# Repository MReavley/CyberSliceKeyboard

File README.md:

# CyberSlice Keyboard

42/36 key split keyboard using RP2040, with the same layout (in 36 key configuration) as my previous design, the Slice 36. The goal was primarily to experience designing a microcontroller directly on the PCB, but I also wanted to try to take advantage of the large number of GPIO pins on the RP2040. There are 8 additional GPIO (2 analog capable) on the PCB with the intention of adding functionality through magnetic pogo connectors, but that is still a work in progress. 

## Features

- Reversible PCB designed for PCB assembly services  
- RP2040 per side, with 16MB of flash  
- Laser cut aluminium plate, custom designed 3D printed case with magnets  
- Footprints for magnetic pogo connectors on each side
- Breakaway tabs convert from 42 to 36 key  

## If you want to build:
This board is just a prototype, and there are a couple pointers to watch out for:

Reversible PCB: Since the PCB is reversible, solder on the trrs connector on opposite sides of the PCB for each half. The USB-C connector for the left half will be on the bottom side, which does necessitate taller rubber feet unfortunately.

Components on the rear:  
These components will not be assembled by basic PCBa, but the parts can be scavenged from spare assembled PCBs (per side)
- C7 (100nF 0603 MLCC capacitor)
- R1 and R2 (5.1k 0603 resistors)
- R12 and R13 (Optional, 4.7k 0603 pullups for split over I2C, not needed for UART)

Additional components:
- PJ320D trrs connectors (x1 per side), solder on opposite side of PCB for the different halves
- 2.54mm magnetic pogo connectors (5 contacts) (2x per side) (optional, can solder directly instead)
- 6mm diameter x 3mm height magnets x6 per side for case (optional, can use screw holes instead)

Reset and boot switches may need to be renamed in the BOM file (not using SW1 and SW2) for them to be auto-selected by PCBa service  
- Otherwise shorting the pads on the PCB will have the same effect

Case:
- Tolerances were very loose on my case, but this does depend on the printer
- Ideally, one would redesign the plate to mount directly to the case (add screw holes)
- Tolerance for the magnet holes can be a bit too tight, probably increase from 6 to 6.1 or 6.2mm diameter

## Things to improve

- Rename the reset and boot switches from SW1 and SW2 to something else to not clash with the names of the switches (caused me to make a mistake in my order)  
- Shift the few SMD parts on the back side to the front for PCBa  
- Add a few more LEDs for status indicators on the PCB itself  
- Change the plate the design for better mounting of PCB and plate to case, or alternatively integrate the plate into the case

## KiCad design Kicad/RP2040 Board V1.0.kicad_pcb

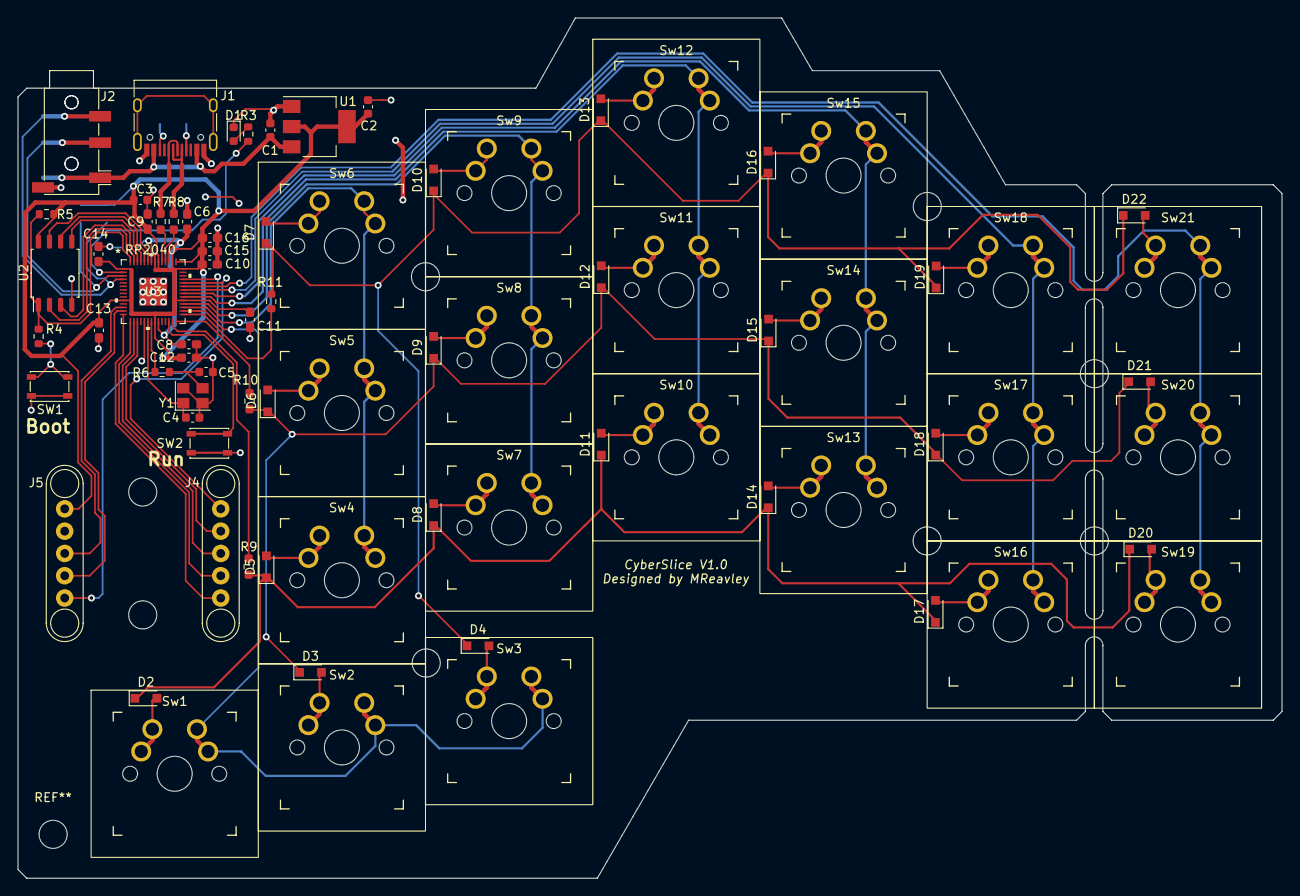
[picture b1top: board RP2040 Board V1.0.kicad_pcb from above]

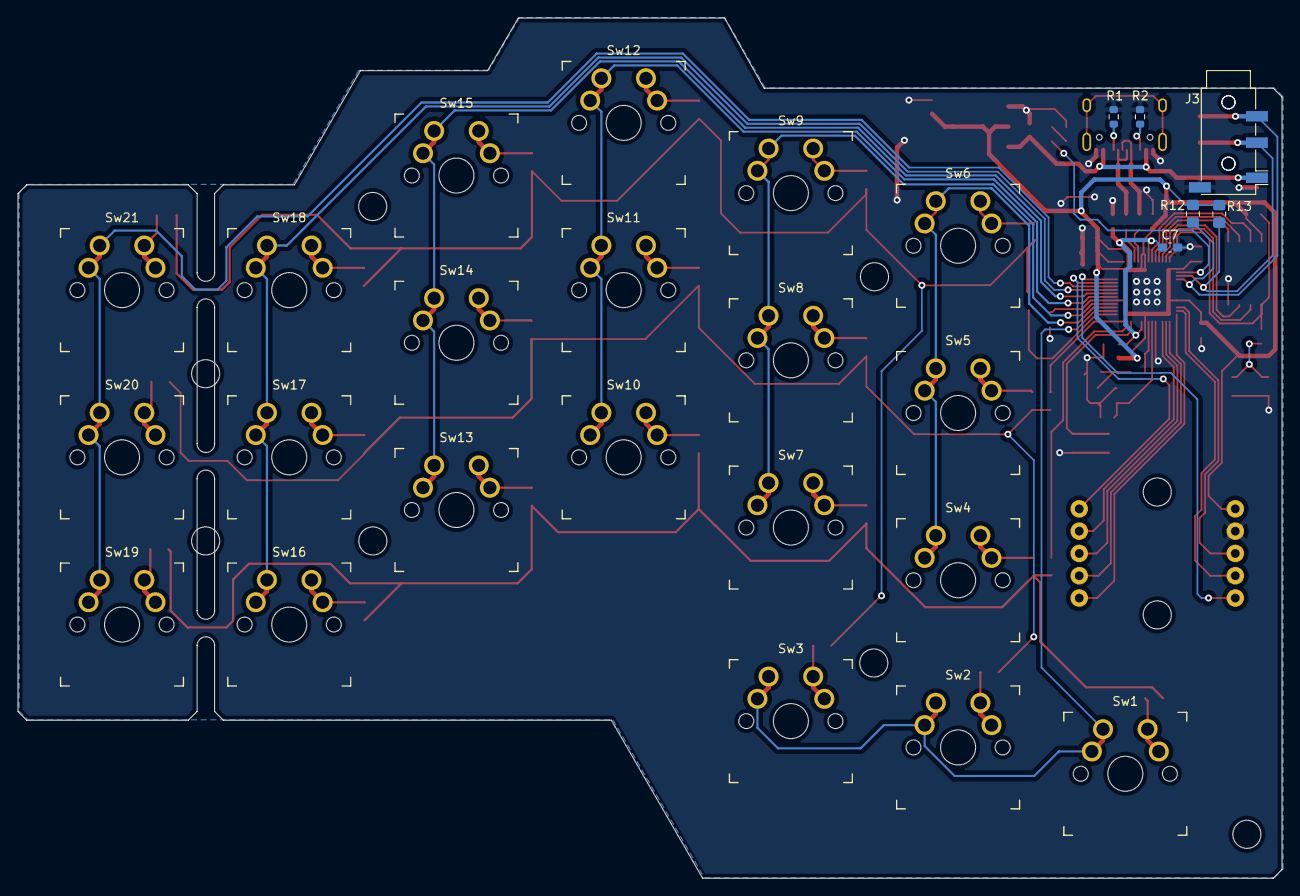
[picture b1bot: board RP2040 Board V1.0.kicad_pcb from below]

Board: 2 copper layers, 144.0 x 98.0 mm, 83 parts (6 on the bottom side), 67 nets.

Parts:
C1, C2: 22u; C_0603_1608Metric
C3: 100n; C_0603_1608Metric
C4, C5: 27p; C_0603_1608Metric
C6, C16: 1u; C_0603_1608Metric_Pad1.08x0.95mm_HandSolder
C7, C8, C9, C10, C11, C12, C13, C14, C15: 100n; C_0603_1608Metric_Pad1.08x0.95mm_HandSolder
D1: RED; LED_0603_1608Metric
D2, D3, D4, D5, D6, D7, D8, D9, D10, D11, D12, D13, D14, D15, D16, D17, D18, D19, D20, D21, D22: D; D_SOD-323_HandSoldering
J1: USB_C_Receptacle_USB2.0; USB_C_Receptacle_HRO_TYPE-C-31-M-12
J2, J3: AudioJack4; Jack_3.5mm_PJ320D_Horizontal
J4, J5: Conn_01x05_MountingPin; Magnet 5pin 2.54mm pitch through hole
R1, R2, R11: 5.1k; R_0603_1608Metric
R3, R4, R6: 1k; R_0603_1608Metric
R5: DNP; R_0603_1608Metric
R7, R8: 27; R_0603_1608Metric_Pad0.98x0.95mm_HandSolder
R9, R10: 5.1k; R_0603_1608Metric_Pad0.98x0.95mm_HandSolder
R12, R13: DNP; R_0805_2012Metric_Pad1.20x1.40mm_HandSolder
SW1, SW2: SW_SPST; SW_SPST_PTS810
Sw1, Sw2, Sw3, Sw4, Sw5, Sw6, Sw7, Sw8, Sw9, Sw10, Sw11, Sw12, Sw13, Sw14, Sw15, Sw16, Sw17, Sw18, Sw19, Sw20, Sw21: Cherry_Doublesided; SW_MX_reversible
U1: AMS1117-3.3; SOT-223-3_TabPin2
U2: W25Q128JVS; SOIC-8_5.23x5.23mm_P1.27mm
U3: RP2040
Y1: 12MHz; Crystal_SMD_3225-4Pin_3.2x2.5mm

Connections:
+1V1: C6.1, C7.1, C8.1, U3.23 (DVDD), U3.45 (VREG_VOUT), U3.50 (DVDD)
+3V3: C2.1, C3.1, C9.1, C10.1, C11.1, C12.1, C13.1, C14.1, C15.1, C16.1, J5.1, R5.2, R12.1, R13.1, U1.2 (VO), U2.8 (VCC), U3.1 (IOVDD), U3.10 (IOVDD), U3.22 (IOVDD), U3.33 (IOVDD), U3.42 (IOVDD), U3.43 (ADC_AVDD), U3.44 (VREG_IN), U3.48 (USB_VDD), U3.49 (IOVDD)
/QSPICLK: U2.6 (CLK), U3.52 (QSPI_SCLK)
/QSPISD0: U2.5 (DI(IO0)), U3.53 (QSPI_SD0)
/QSPISD2: U2.3 (IO2), U3.54 (QSPI_SD2)
/QSPISD3: U2.7 (IO3), U3.51 (QSPI_SD3)
/QSPISS: R4.1, R5.1, U2.1 (~CS), U3.56 (QSPI_SS)
/SQPISD1: U2.2 (DO(IO1)), U3.55 (QSPI_SD1)
Col 0: Sw1.2 (SW), Sw2.2 (SW), Sw3.2 (NW), U3.30 (GPIO19)
Col 1: Sw4.2 (SW), Sw5.2 (NW), Sw6.2 (NW), U3.31 (GPIO20)
Col 2: Sw7.2 (SW), Sw8.2 (NW), Sw9.2 (NW), U3.32 (GPIO21)
Col 3: Sw10.2 (SW), Sw11.2 (NW), Sw12.2 (NW), U3.34 (GPIO22)
Col 4: Sw13.2 (NW), Sw14.2 (NW), Sw15.2 (NW), U3.35 (GPIO23)
Col 5: Sw16.2 (SW), Sw17.2 (NW), Sw18.2 (NW), U3.36 (GPIO24)
Col 6: Sw19.2 (SW), Sw20.2 (SW), Sw21.2 (NW), U3.37 (GPIO25)
Data+: J1.A6 (D+), J1.B6 (D+), R7.2
Data-: J1.A7 (D-), J1.B7 (D-), R8.2
GND: C1.2, C2.2, C3.2, C4.2, C5.2, C6.2, C7.2, C8.2, C9.2, C10.2, C11.2, C12.2, C13.2, C14.2, C15.2, C16.2, D1.1 (K), J1.A1 (GND), J1.A12 (GND), J1.B1 (GND), J1.B12 (GND), J2.S, J3.S, J5.2, R1.1, R2.1, SW1.1 (A), SW2.1 (A), U1.1 (GND), U2.4 (GND), U3.19 (TESTEN), U3.57 (GND), Y1.2, Y1.4
LED: R3.2, U3.2 (GPIO0)
unnamed: C4.1, U3.20 (XIN), Y1.1
unnamed: C5.1, R6.2, Y1.3
unnamed: D1.2 (A), R3.1
unnamed: D2.2 (A), Sw1.1 (NE)
unnamed: D3.2 (A), Sw2.1 (NE)
unnamed: D4.2 (A), Sw3.1 (NE)
unnamed: D5.2 (A), Sw4.1 (NE)
unnamed: D6.2 (A), Sw5.1 (NE)
unnamed: D7.2 (A), Sw6.1 (NE)
unnamed: D8.2 (A), Sw7.1 (NE)
unnamed: D9.2 (A), Sw8.1 (NE)
unnamed: D4.1 (K), D7.1 (K), D10.1 (K), D13.1 (K), D16.1 (K), D19.1 (K), D22.1 (K), R11.2
unnamed: D10.2 (A), Sw9.1 (NE)
unnamed: D2.1 (K), D5.1 (K), D8.1 (K), D11.1 (K), D14.1 (K), D17.1 (K), D20.1 (K), R9.2
unnamed: D11.2 (A), Sw10.1 (NE)
unnamed: D3.1 (K), D6.1 (K), D9.1 (K), D12.1 (K), D15.1 (K), D18.1 (K), D21.1 (K), R10.2
unnamed: D12.2 (A), Sw11.1 (NE)
unnamed: D13.2 (A), Sw12.1 (NE)
unnamed: D14.2 (A), Sw13.1 (NE)
unnamed: D15.2 (A), Sw14.1 (NE)
unnamed: D16.2 (A), Sw15.1 (NE)
unnamed: D17.2 (A), Sw16.1 (NE)
unnamed: D18.2 (A), Sw17.1 (NE)
unnamed: D19.2 (A), Sw18.1 (NE)
unnamed: D20.2 (A), Sw19.1 (NE)
unnamed: D21.2 (A), Sw20.1 (NE)
unnamed: D22.2 (A), Sw21.1 (NE)
unnamed: J1.A5 (CC1), R1.2
unnamed: J1.B5 (CC2), R2.2
unnamed: J2.R2, J3.R2, R12.2, U3.4 (GPIO2)
unnamed: J4.1, U3.38 (GPIO26_ADC0)
unnamed: J4.2, U3.17 (GPIO14)
unnamed: J4.3, U3.16 (GPIO13)
unnamed: J4.4, U3.15 (GPIO12)
unnamed: J4.5, U3.14 (GPIO11)
unnamed: J5.3, U3.12 (GPIO9)
unnamed: J5.4, U3.13 (GPIO10)
unnamed: J5.5, U3.39 (GPIO27_ADC1)
unnamed: R4.2, SW1.2 (B)
unnamed: R6.1, U3.21 (XOUT)
unnamed: R7.1, U3.47 (USB_DP)
unnamed: R8.1, U3.46 (USB_DM)
unnamed: SW2.2 (B), U3.26 (RUN)
unnamed: J2.R1, J3.R1, R13.2, U3.3 (GPIO1)
Row 0: R9.1, U3.27 (GPIO16)
Row 1: R10.1, U3.28 (GPIO17)
Row 2: R11.1, U3.29 (GPIO18)
VBUS: C1.1, J1.A4 (VBUS), J1.A9 (VBUS), J1.B4 (VBUS), J1.B9 (VBUS), J2.T, J3.T, U1.3 (VI)

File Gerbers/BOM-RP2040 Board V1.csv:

Comment,Designator,Footprint,LCSC
100n,"C10,C11,C12,C13,C14,C15,C3,C7,C8,C9",C_0603_1608Metric_Pad1.08x0.95mm_HandSolder,C14663
1u,"C16,C6",C_0603_1608Metric_Pad1.08x0.95mm_HandSolder,C1592
USB_C_Receptacle_USB2.0,J1,USB_C_Receptacle_HRO_TYPE-C-31-M-12,C165948
RP2040,U3,RP2040,C2040
1k,"R3,R4,R6",R_0603_1608Metric,C21190
D,"D10,D11,D12,D13,D14,D15,D16,D17,D18,D19,D2,D20,D21,D22,D3,D4,D5,D6,D7,D8,D9",D_SOD-323_HandSoldering,C2128
SW_SPST,"SW1,SW2",SW_SPST_PTS810,C221895
5.1k,"R1,R10,R11,R2,R9",R_0603_1608Metric,C23186
27,"R7,R8",R_0603_1608Metric_Pad0.98x0.95mm_HandSolder,C25190
12MHz,Y1,Crystal_SMD_3225-4Pin_3.2x2.5mm,C390764
22u,"C1,C2",C_0603_1608Metric,C59461
AMS1117-3.3,U1,SOT-223-3_TabPin2,C6186
RED,D1,LED_0603_1608Metric,C84263
27p,"C4,C5",C_0603_1608Metric,C92670
W25Q128JVS,U2,SOIC-8_5.23x5.23mm_P1.27mm,C97521
Cherry_Doublesided,Sw14,SW_MX_reversible,
Cherry_Doublesided,Sw7,SW_MX_reversible,
Cherry_Doublesided,Sw3,SW_MX_reversible,
Cherry_Doublesided,Sw6,SW_MX_reversible,
Cherry_Doublesided,Sw12,SW_MX_reversible,
Cherry_Doublesided,Sw17,SW_MX_reversible,
Cherry_Doublesided,Sw8,SW_MX_reversible,
Cherry_Doublesided,Sw9,SW_MX_reversible,
Cherry_Doublesided,Sw20,SW_MX_reversible,
Conn_01x05_MountingPin,J4,Magnet 5pin 2.54mm pitch through hole,
Cherry_Doublesided,Sw21,SW_MX_reversible,
Cherry_Doublesided,Sw11,SW_MX_reversible,
DNP,R5,R_0603_1608Metric,
Cherry_Doublesided,Sw2,SW_MX_reversible,
Cherry_Doublesided,Sw1,SW_MX_reversible,
Cherry_Doublesided,Sw4,SW_MX_reversible,
Cherry_Doublesided,Sw13,SW_MX_reversible,
Cherry_Doublesided,Sw19,SW_MX_reversible,
Cherry_Doublesided,Sw15,SW_MX_reversible,
Conn_01x05_MountingPin,J5,Magnet 5pin 2.54mm pitch through hole,
AudioJack4,J2,Jack_3.5mm_PJ320D_Horizontal,
Cherry_Doublesided,Sw10,SW_MX_reversible,
Cherry_Doublesided,Sw5,SW_MX_reversible,
Cherry_Doublesided,Sw18,SW_MX_reversible,
Cherry_Doublesided,Sw16,SW_MX_reversible,
AudioJack4,J3,Jack_3.5mm_PJ320D_Horizontal,
DNP,R12,R_0805_2012Metric_Pad1.20x1.40mm_HandSolder,
DNP,R13,R_0805_2012Metric_Pad1.20x1.40mm_HandSolder,

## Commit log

2022-08-30 Add files via upload
    Photos

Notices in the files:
parts and their libraries:
Copyright 2021 Accelerated Designs. All rights reserved.
